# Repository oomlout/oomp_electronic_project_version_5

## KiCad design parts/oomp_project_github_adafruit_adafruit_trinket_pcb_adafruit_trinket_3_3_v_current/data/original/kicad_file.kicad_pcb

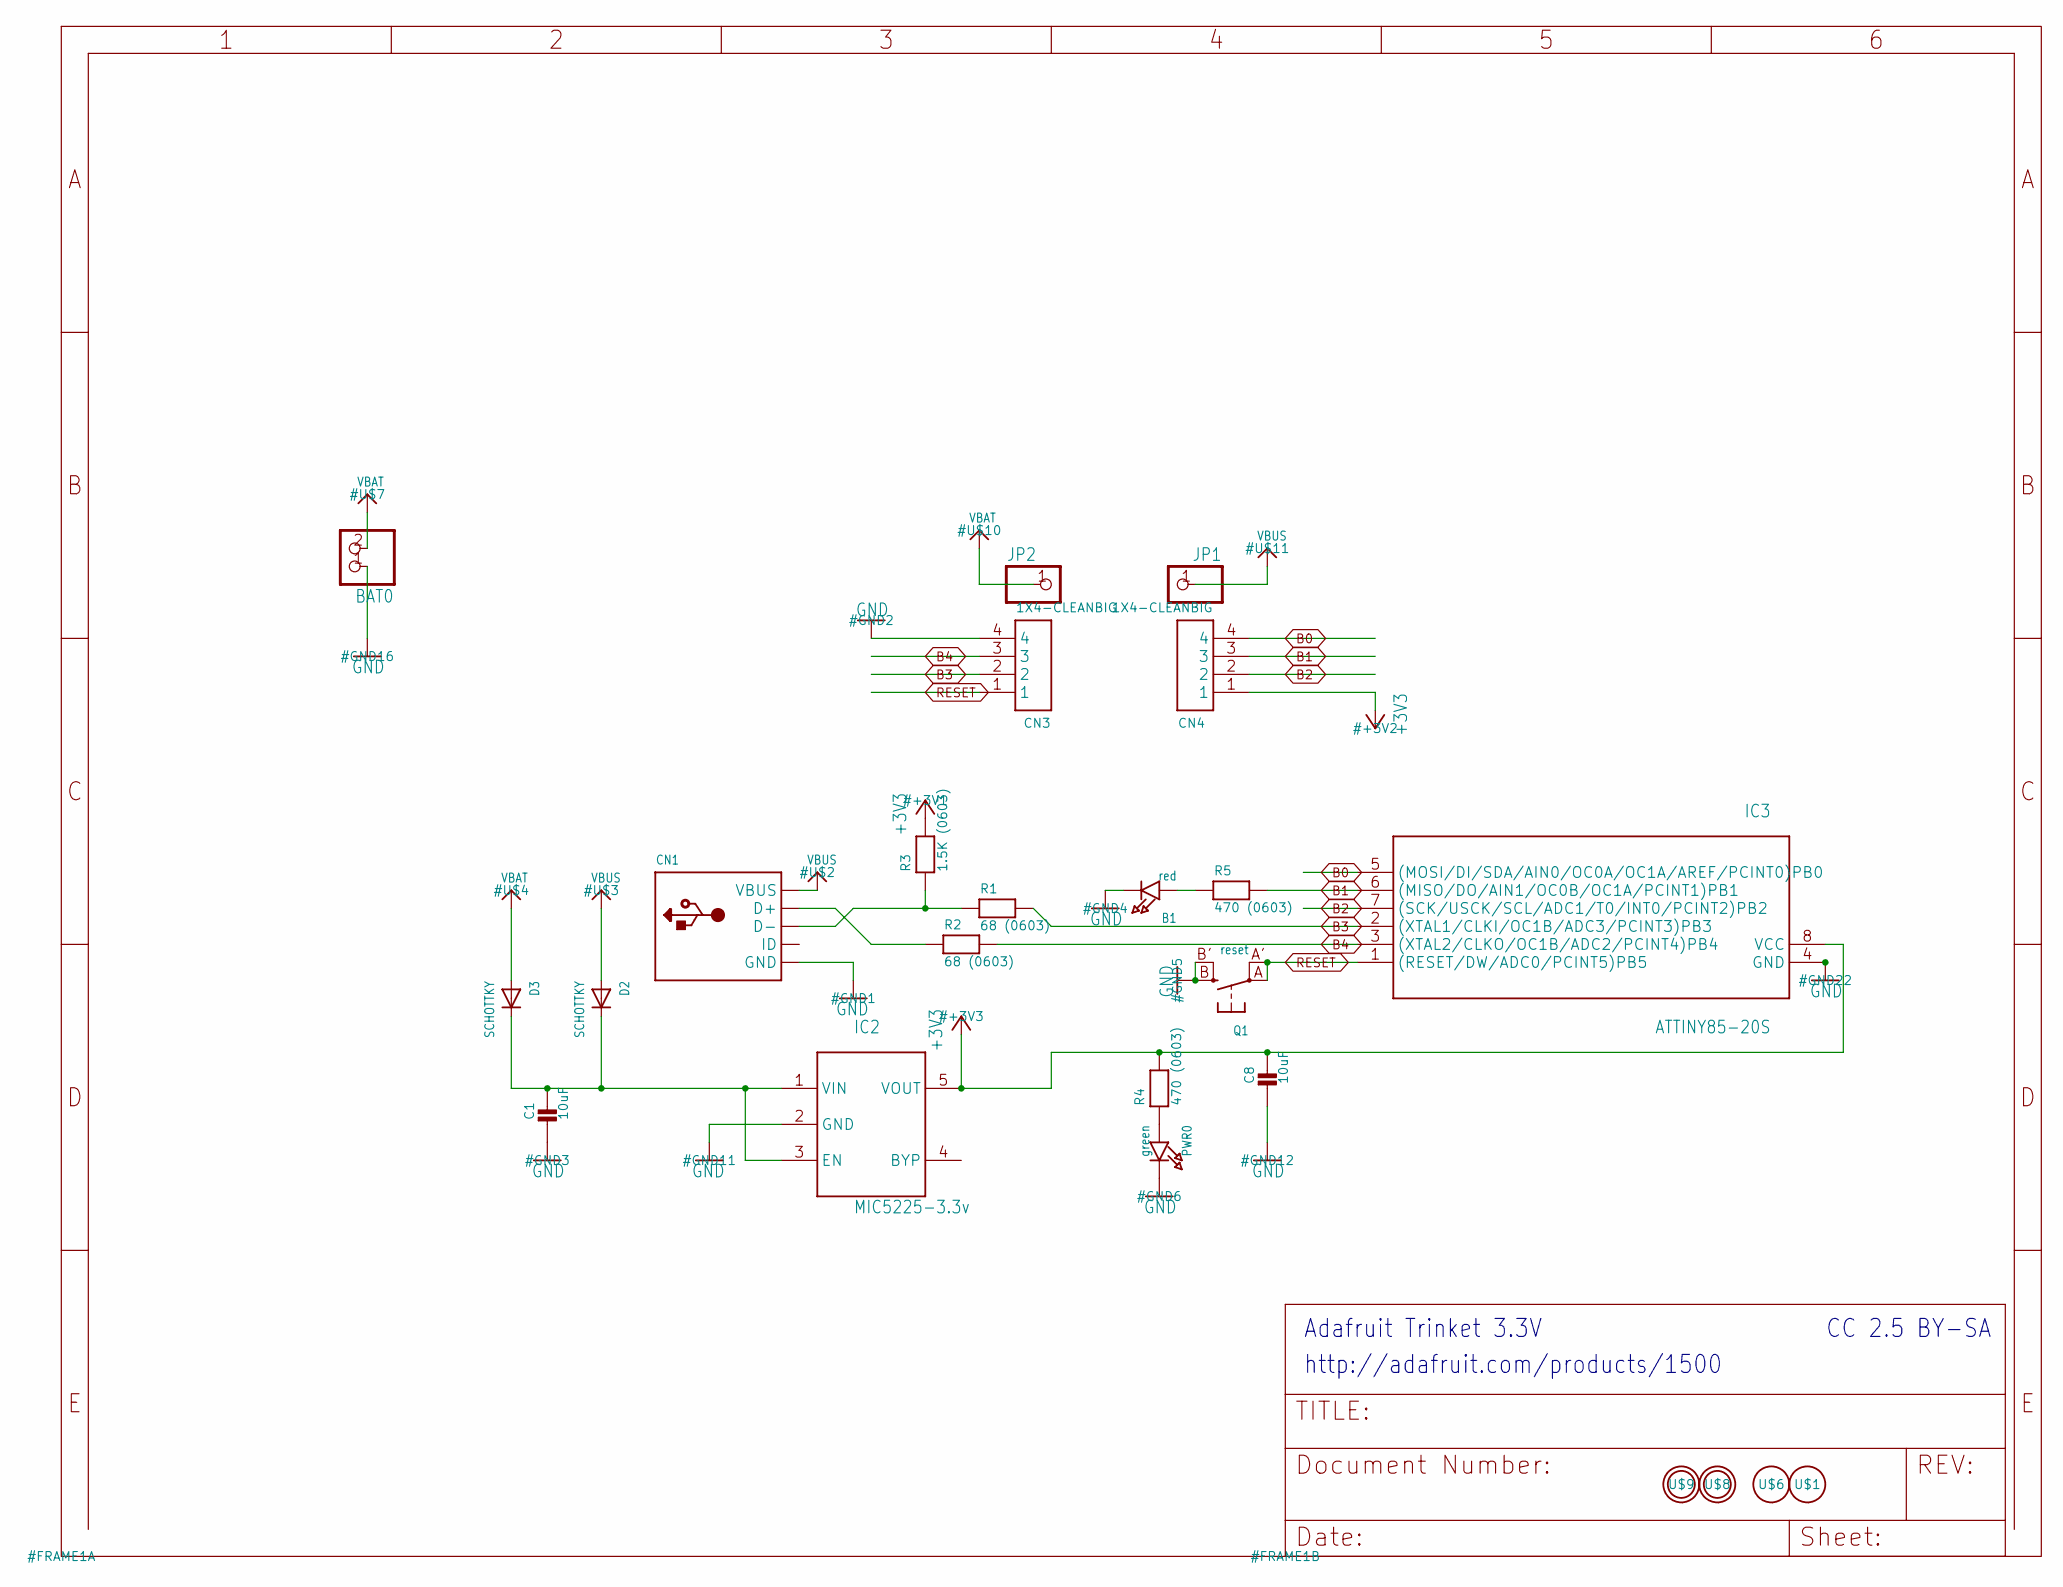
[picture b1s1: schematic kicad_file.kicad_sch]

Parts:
B1: red; CHIPLED_0805_NOOUTLINE
BAT0: CON_JST_PH_2PIN; JSTPH2
C1, C8: 10uF; 0805-NO
CN1: USBMINIB; USB-MINIB
CN3, CN4: 1X4-CLEANBIG; 1X04-CLEANBIG
D2, D3: SCHOTTKY; SOD-123FL
IC2: MIC5225-3.3v; SOT23-5L
IC3: ATTINY85-20S; SOIC8
JP1, JP2: PINHD-1X1CB; 1X01-CLEANBIG
PWR0: green; CHIPLED_0805_NOOUTLINE
Q1: reset; BTN_KMR2_4.6X2.8
R1, R2: 68 (0603); 0603-NO
R3: 1.5K (0603); 0603-NO
R4, R5: 470 (0603); 0603-NO
U$1, U$6: FIDUCIAL; FIDUCIAL_1MM
U$8, U$9: MOUNTINGHOLE2.0; MOUNTINGHOLE_2.0_PLATED

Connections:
+3V3: C8.1, CN4.1, IC2.5 (VOUT), IC3.8 (VCC), R3.2, R4.2
B0: CN4.4, IC3.5 ((MOSI/DI/SDA/AIN0/OC0A/OC1A/AREF/PCINT0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)
B1: CN4.3, IC3.6 ((MISO/DO/AIN1/OC0B/OC1A/PCINT1)PB1), R5.2
B2: CN4.2, IC3.7 ((SCK/USCK/SCL/ADC1/T0/INT0/PCINT2)PB2)
B3: CN3.2, IC3.2 ((XTAL1/CLKI/OC1B/ADC3/PCINT3)PB3), R1.2
B4: CN3.3, IC3.3 ((XTAL2/CLKO/OC1B/ADC2/PCINT4)PB4), R2.2
D+: CN1.D+, R2.1
D-: CN1.D-, R1.1, R3.1
GND: B1.C, BAT0.1, C1.2, C8.2, CN1.GND, CN1.GND1 (GND), CN1.GND2 (GND), CN1.GND3 (GND), CN1.GND4 (GND), CN3.4, IC2.2 (GND), IC3.4 (GND), PWR0.C, Q1.B (S), Q1.B' (S1)
unnamed: B1.A, R5.1
unnamed: PWR0.A, R4.1
unnamed: C1.1, D2.C, D3.C, IC2.1 (VIN), IC2.3 (EN)
RESET: CN3.1, IC3.1 ((RESET/DW/ADC0/PCINT5)PB5), Q1.A, Q1.A' (P1)
VBAT: BAT0.2, D3.A, JP2.1
VBUS: CN1.VBUS, D2.A, JP1.1

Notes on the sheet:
CC 2.5 BY-SA
http://adafruit.com/products/1500
Adafruit Trinket 3.3V

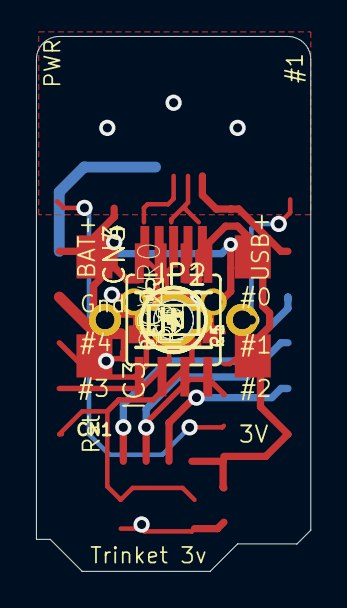
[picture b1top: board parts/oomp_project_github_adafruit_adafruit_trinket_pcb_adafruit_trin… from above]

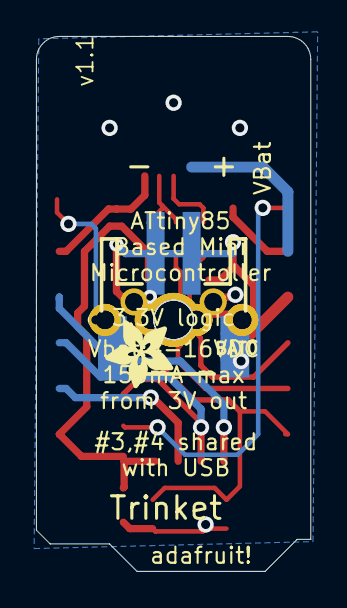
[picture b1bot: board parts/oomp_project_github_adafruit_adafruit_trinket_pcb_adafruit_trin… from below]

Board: 16 copper layers, 15.2 x 29.7 mm, 27 parts (2 on the bottom side), 15 nets.

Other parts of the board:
U$5: ADAFRUIT_3.5MM
UNK_HOLE_0: dummyfp0
UNK_HOLE_1: dummyfp1

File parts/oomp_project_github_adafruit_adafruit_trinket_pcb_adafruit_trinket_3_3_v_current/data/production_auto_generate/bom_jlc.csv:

Comment,Designator,Footprint,LCSC Part #
,"JP1,JP2",Adafruit Trinket 3.3V-import-fps:1X01-CLEANBIG,C7501259
,U$5,Adafruit Trinket 3.3V-import-fps:ADAFRUIT_3.5MM,
,BAT0,Adafruit Trinket 3.3V-import-fps:JSTPH2,
,CN1,Adafruit Trinket 3.3V-import-fps:USB-MINIB,
1.5K (0603),R3,Adafruit Trinket 3.3V-import-fps:0603-NO,C2930050
10uF,"C1,C8",Adafruit Trinket 3.3V-import-fps:0805-NO,
1X4-CLEANBIG,"CN3,CN4",Adafruit Trinket 3.3V-import-fps:1X04-CLEANBIG,
470 (0603),"R4,R5",Adafruit Trinket 3.3V-import-fps:0603-NO,C23179
68 (0603),"R1,R2",Adafruit Trinket 3.3V-import-fps:0603-NO,C27592
ATTINY85-20S,IC3,Adafruit Trinket 3.3V-import-fps:SOIC8,
FIDUCIAL,"U$1,U$6",Adafruit Trinket 3.3V-import-fps:FIDUCIAL_1MM,
green,PWR0,Adafruit Trinket 3.3V-import-fps:CHIPLED_0805_NOOUTLINE,
MIC5225-3.3v,IC2,Adafruit Trinket 3.3V-import-fps:SOT23-5L,
red,B1,Adafruit Trinket 3.3V-import-fps:CHIPLED_0805_NOOUTLINE,
reset,Q1,Adafruit Trinket 3.3V-import-fps:BTN_KMR2_4.6X2.8,
SCHOTTKY,"D2,D3",Adafruit Trinket 3.3V-import-fps:SOD-123FL,

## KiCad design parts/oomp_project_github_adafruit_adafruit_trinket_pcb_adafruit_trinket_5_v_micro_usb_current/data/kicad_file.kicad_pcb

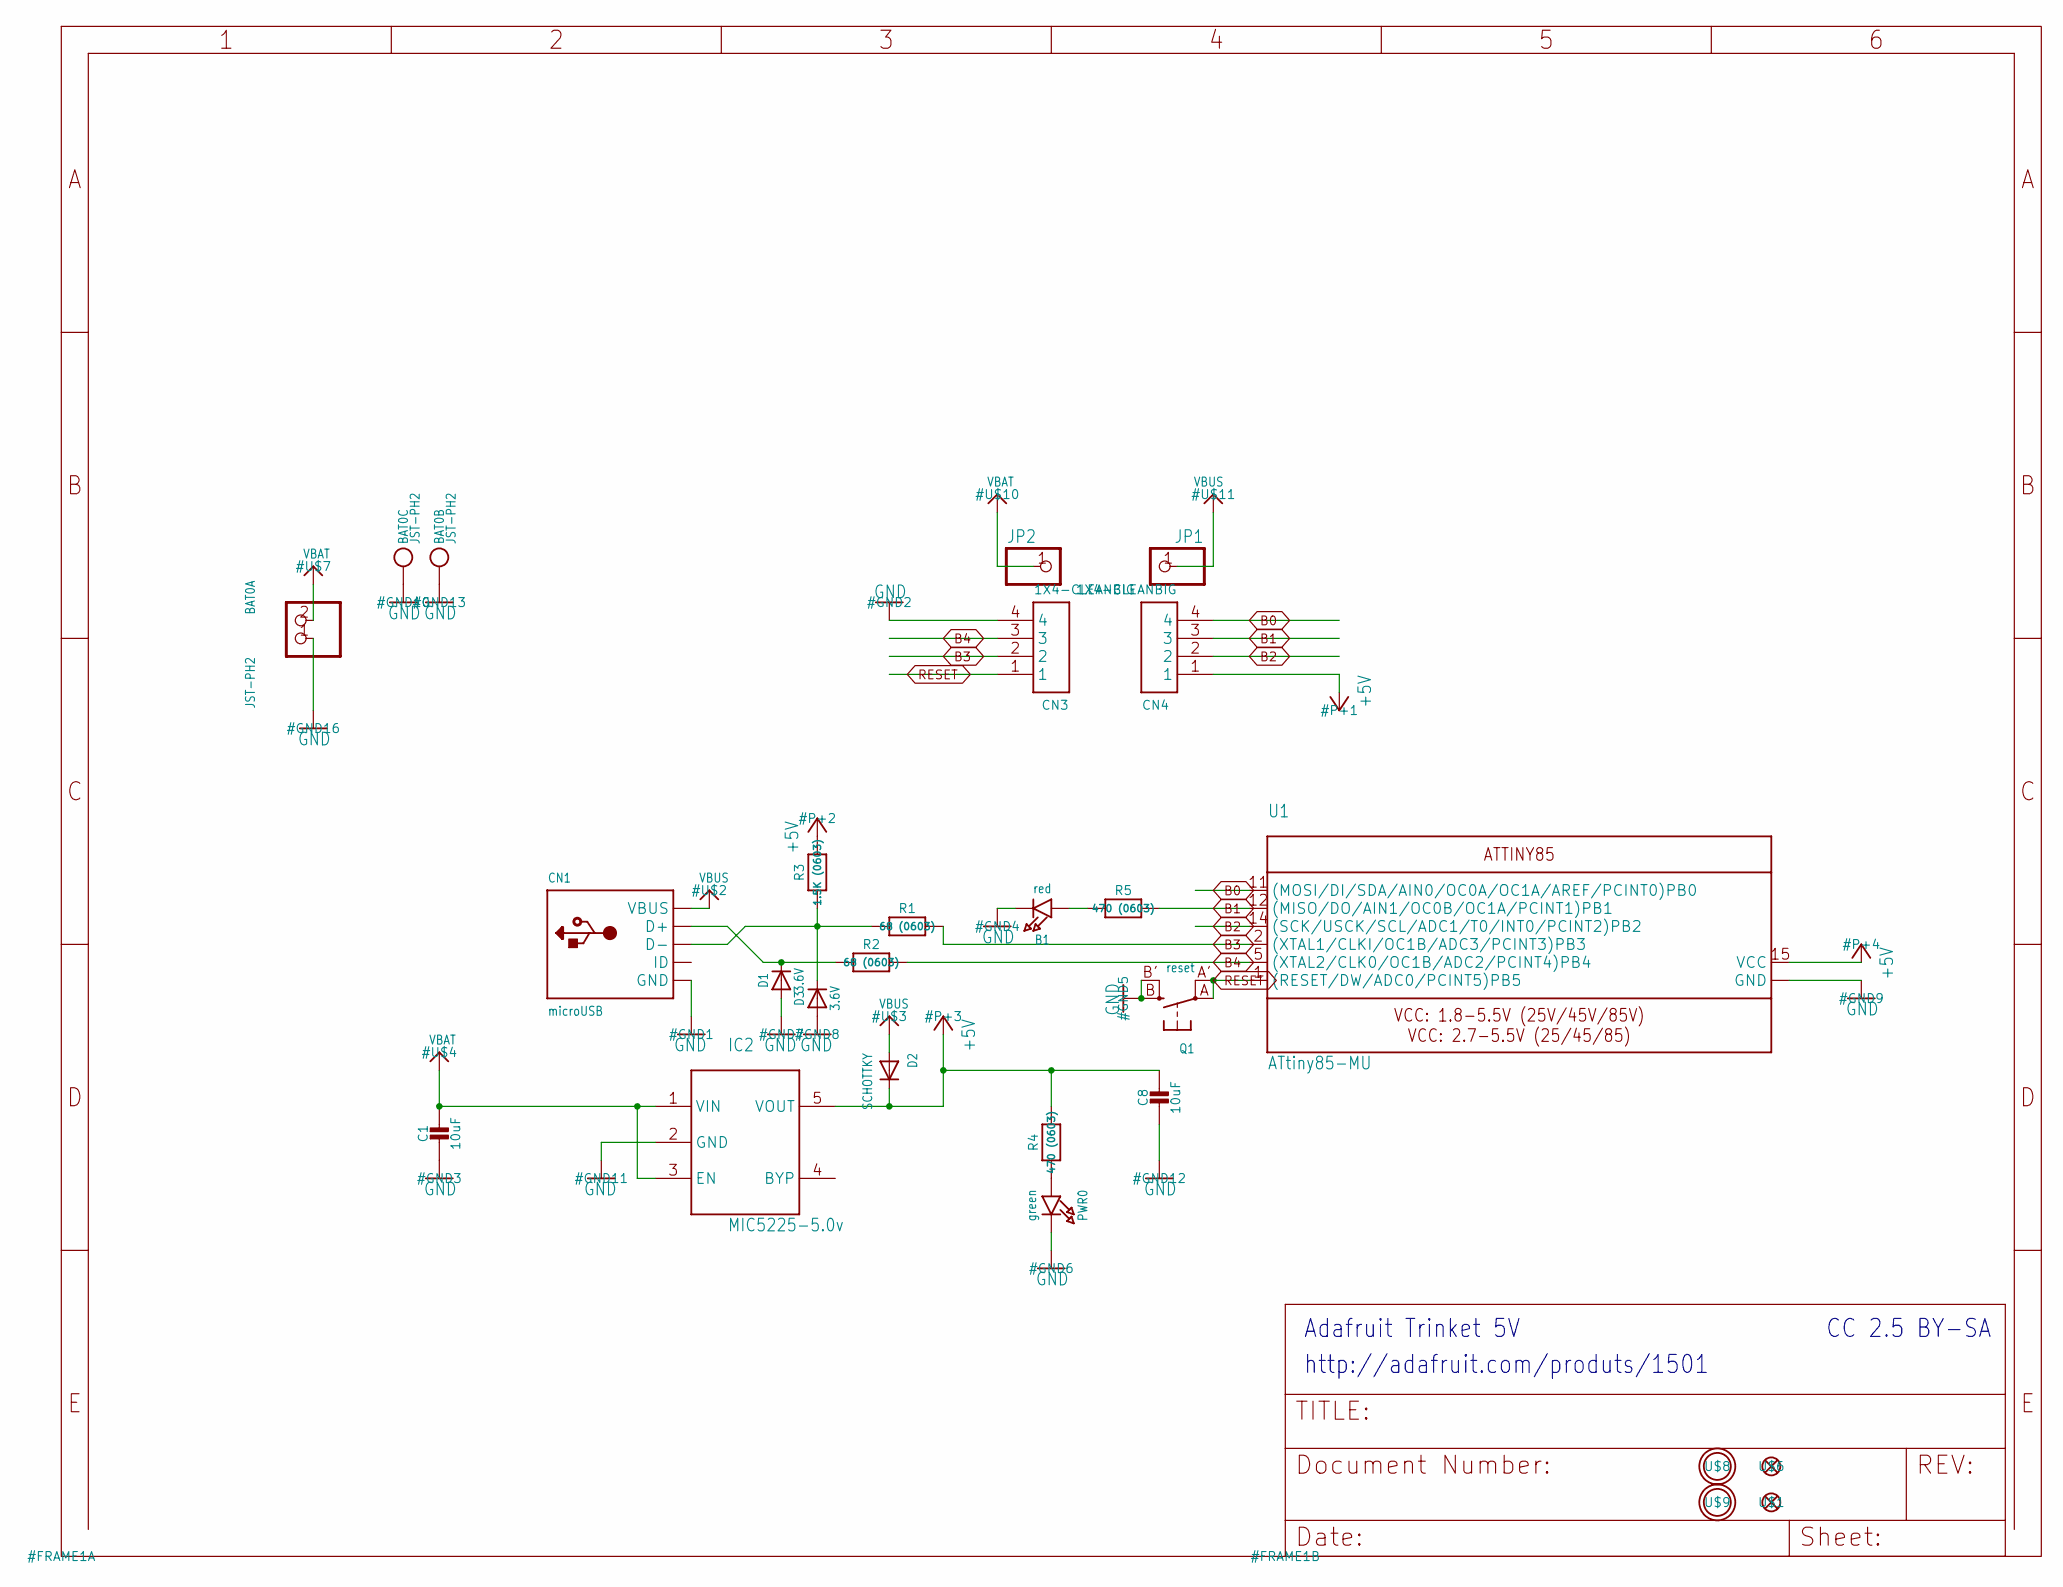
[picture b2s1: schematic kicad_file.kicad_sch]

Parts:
B1: red; CHIPLED_0805_NOOUTLINE
BAT0: JST-PH2; JSTPH2
C1, C8: 10uF; 0805-NO
CN1: microUSB; 4UCONN_20329
CN3, CN4: 1X4-CLEANBIG; 1X04-CLEANBIG
D1, D3: 3.6V; SOD-323
D2: SCHOTTKY; SOD-123FL
IC2: MIC5225-5.0v; SOT23-5L
JP1, JP2: PINHD-1X1CB; 1X01-CLEANBIG
PWR0: green; CHIPLED_0805_NOOUTLINE
Q1: reset; BTN_KMR2_4.6X2.8
R1, R2: 68 (0603); 0603-NO
R3: 1.5K (0603); 0603-NO
R4, R5: 470 (0603); 0603-NO
U1: ATtiny85-MU; MLF20_4X4MM_0.5MM_ATMEL
U$1, U$6: FIDUCIAL""; FIDUCIAL_1MM
U$8, U$9: MOUNTINGHOLE2.0; MOUNTINGHOLE_2.0_PLATED

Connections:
+5V: C8.1, CN4.1, D2.C, IC2.5 (VOUT), R3.2, R4.2, U1.15 (VCC)
B0: CN4.4, U1.11 ((MOSI/DI/SDA/AIN0/OC0A/OC1A/AREF/PCINT0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)
B1: CN4.3, R5.2, U1.12 ((MISO/DO/AIN1/OC0B/OC1A/PCINT1)PB1)
B2: CN4.2, U1.14 ((SCK/USCK/SCL/ADC1/T0/INT0/PCINT2)PB2)
B3: CN3.2, R1.2, U1.2 ((XTAL1/CLKI/OC1B/ADC3/PCINT3)PB3)
B4: CN3.3, R2.2, U1.5 ((XTAL2/CLK0/OC1B/ADC2/PCINT4)PB4)
GND: B1.C, BAT0.1, BAT0.NC1, BAT0.NC2, C1.2, C8.2, CN1.BASE@1 (GND), CN1.BASE@2 (GND), CN1.GND, CN1.SPRT@1 (GND), CN1.SPRT@2 (GND), CN1.SPRT@3 (GND), CN1.SPRT@4 (GND), CN3.4, D1.A, D3.A, IC2.2 (GND), PWR0.C, Q1.B (S), Q1.B' (S1), U1.8 (GND), U1.THERMAL (GND)
unnamed: B1.A, R5.1
unnamed: CN1.D+, D1.C, R2.1
unnamed: CN1.D-, D3.C, R1.1, R3.1
unnamed: PWR0.A, R4.1
RESET: CN3.1, Q1.A, Q1.A' (P1), U1.1 ((RESET/DW/ADC0/PCINT5)PB5)
VBAT: BAT0.2, C1.1, IC2.1 (VIN), IC2.3 (EN), JP2.1
VBUS: CN1.VBUS, D2.A, JP1.1

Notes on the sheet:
CC 2.5 BY-SA
http://adafruit.com/produts/1501
Adafruit Trinket 5V

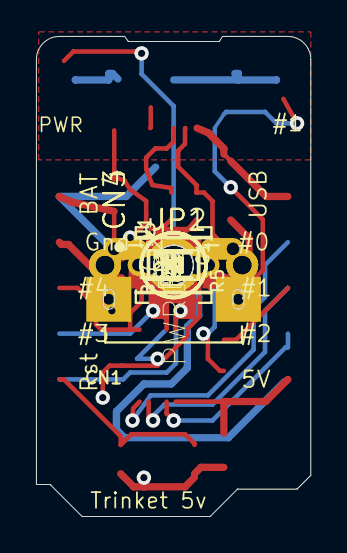
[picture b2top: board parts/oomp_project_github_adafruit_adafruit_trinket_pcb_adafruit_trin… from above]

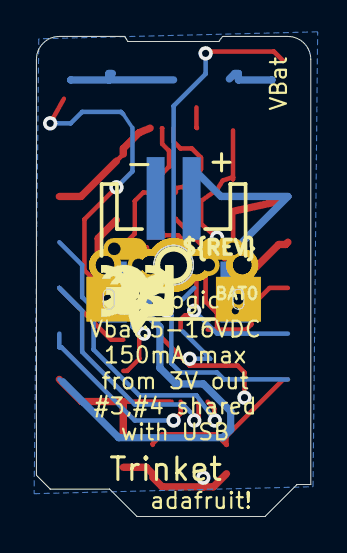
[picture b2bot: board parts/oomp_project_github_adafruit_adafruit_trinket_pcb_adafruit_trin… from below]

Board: 16 copper layers, 15.2 x 26.7 mm, 31 parts (5 on the bottom side), 14 nets.

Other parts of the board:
U$5: ADAFRUIT_3.5MM
U$12: PCBFEAT-REV-040
U$13: SYMBOL_FCC_TINY
U$14: SYMBOL_CE_TINY
UNK_HOLE_0: dummyfp0
UNK_HOLE_1: dummyfp1

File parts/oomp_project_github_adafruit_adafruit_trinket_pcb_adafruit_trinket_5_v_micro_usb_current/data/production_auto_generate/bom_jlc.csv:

Comment,Designator,Footprint,LCSC Part #
,"JP1,JP2",Adafruit Trinket 5V microUSB-import-fps:1X01-CLEANBIG,C7501259
,U$5,Adafruit Trinket 5V microUSB-import-fps:ADAFRUIT_3.5MM,
,U$12,Adafruit Trinket 5V microUSB-import-fps:PCBFEAT-REV-040,
,U$14,Adafruit Trinket 5V microUSB-import-fps:SYMBOL_CE_TINY,
,U$13,Adafruit Trinket 5V microUSB-import-fps:SYMBOL_FCC_TINY,
1.5K (0603),R3,Adafruit Trinket 5V microUSB-import-fps:0603-NO,C2930050
10uF,"C1,C8",Adafruit Trinket 5V microUSB-import-fps:0805-NO,
1X4-CLEANBIG,"CN3,CN4",Adafruit Trinket 5V microUSB-import-fps:1X04-CLEANBIG,
3.6V,"D1,D3",Adafruit Trinket 5V microUSB-import-fps:SOD-323,
470 (0603),"R4,R5",Adafruit Trinket 5V microUSB-import-fps:0603-NO,C23179
68 (0603),"R1,R2",Adafruit Trinket 5V microUSB-import-fps:0603-NO,C27592
ATtiny85-MU,U1,Adafruit Trinket 5V microUSB-import-fps:MLF20_4X4MM_0.5MM_ATMEL,
"FIDUCIAL""""","U$1,U$6",Adafruit Trinket 5V microUSB-import-fps:FIDUCIAL_1MM,
green,PWR0,Adafruit Trinket 5V microUSB-import-fps:CHIPLED_0805_NOOUTLINE,
JST-PH2,BAT0,Adafruit Trinket 5V microUSB-import-fps:JSTPH2,
MIC5225-5.0v,IC2,Adafruit Trinket 5V microUSB-import-fps:SOT23-5L,
microUSB,CN1,Adafruit Trinket 5V microUSB-import-fps:4UCONN_20329,
red,B1,Adafruit Trinket 5V microUSB-import-fps:CHIPLED_0805_NOOUTLINE,
reset,Q1,Adafruit Trinket 5V microUSB-import-fps:BTN_KMR2_4.6X2.8,
SCHOTTKY,D2,Adafruit Trinket 5V microUSB-import-fps:SOD-123FL,

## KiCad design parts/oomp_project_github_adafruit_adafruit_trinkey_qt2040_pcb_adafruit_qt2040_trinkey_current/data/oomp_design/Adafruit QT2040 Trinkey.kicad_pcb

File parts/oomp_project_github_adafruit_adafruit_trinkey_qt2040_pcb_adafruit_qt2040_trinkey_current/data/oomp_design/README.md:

# OOMP KiCad design copy

Open `Adafruit QT2040 Trinkey.kicad_pro` (or the `.kicad_pcb` / `.kicad_sch`) in KiCad. Local OOMP libraries are under `libraries/`. Original inputs are preserved in [../original/](../original/).

Only verified unchanged installed KiCad defaults were renamed. Modified, custom, unmatched and unavailable items remain unchanged. Soldering variants are never swapped during conversion. Existing pad coordinates, nets and UUIDs are preserved.

See [conversion_report.yaml](conversion_report.yaml) for every conversion and skip. Copy this directory before editing; regeneration refuses to overwrite edited design files.

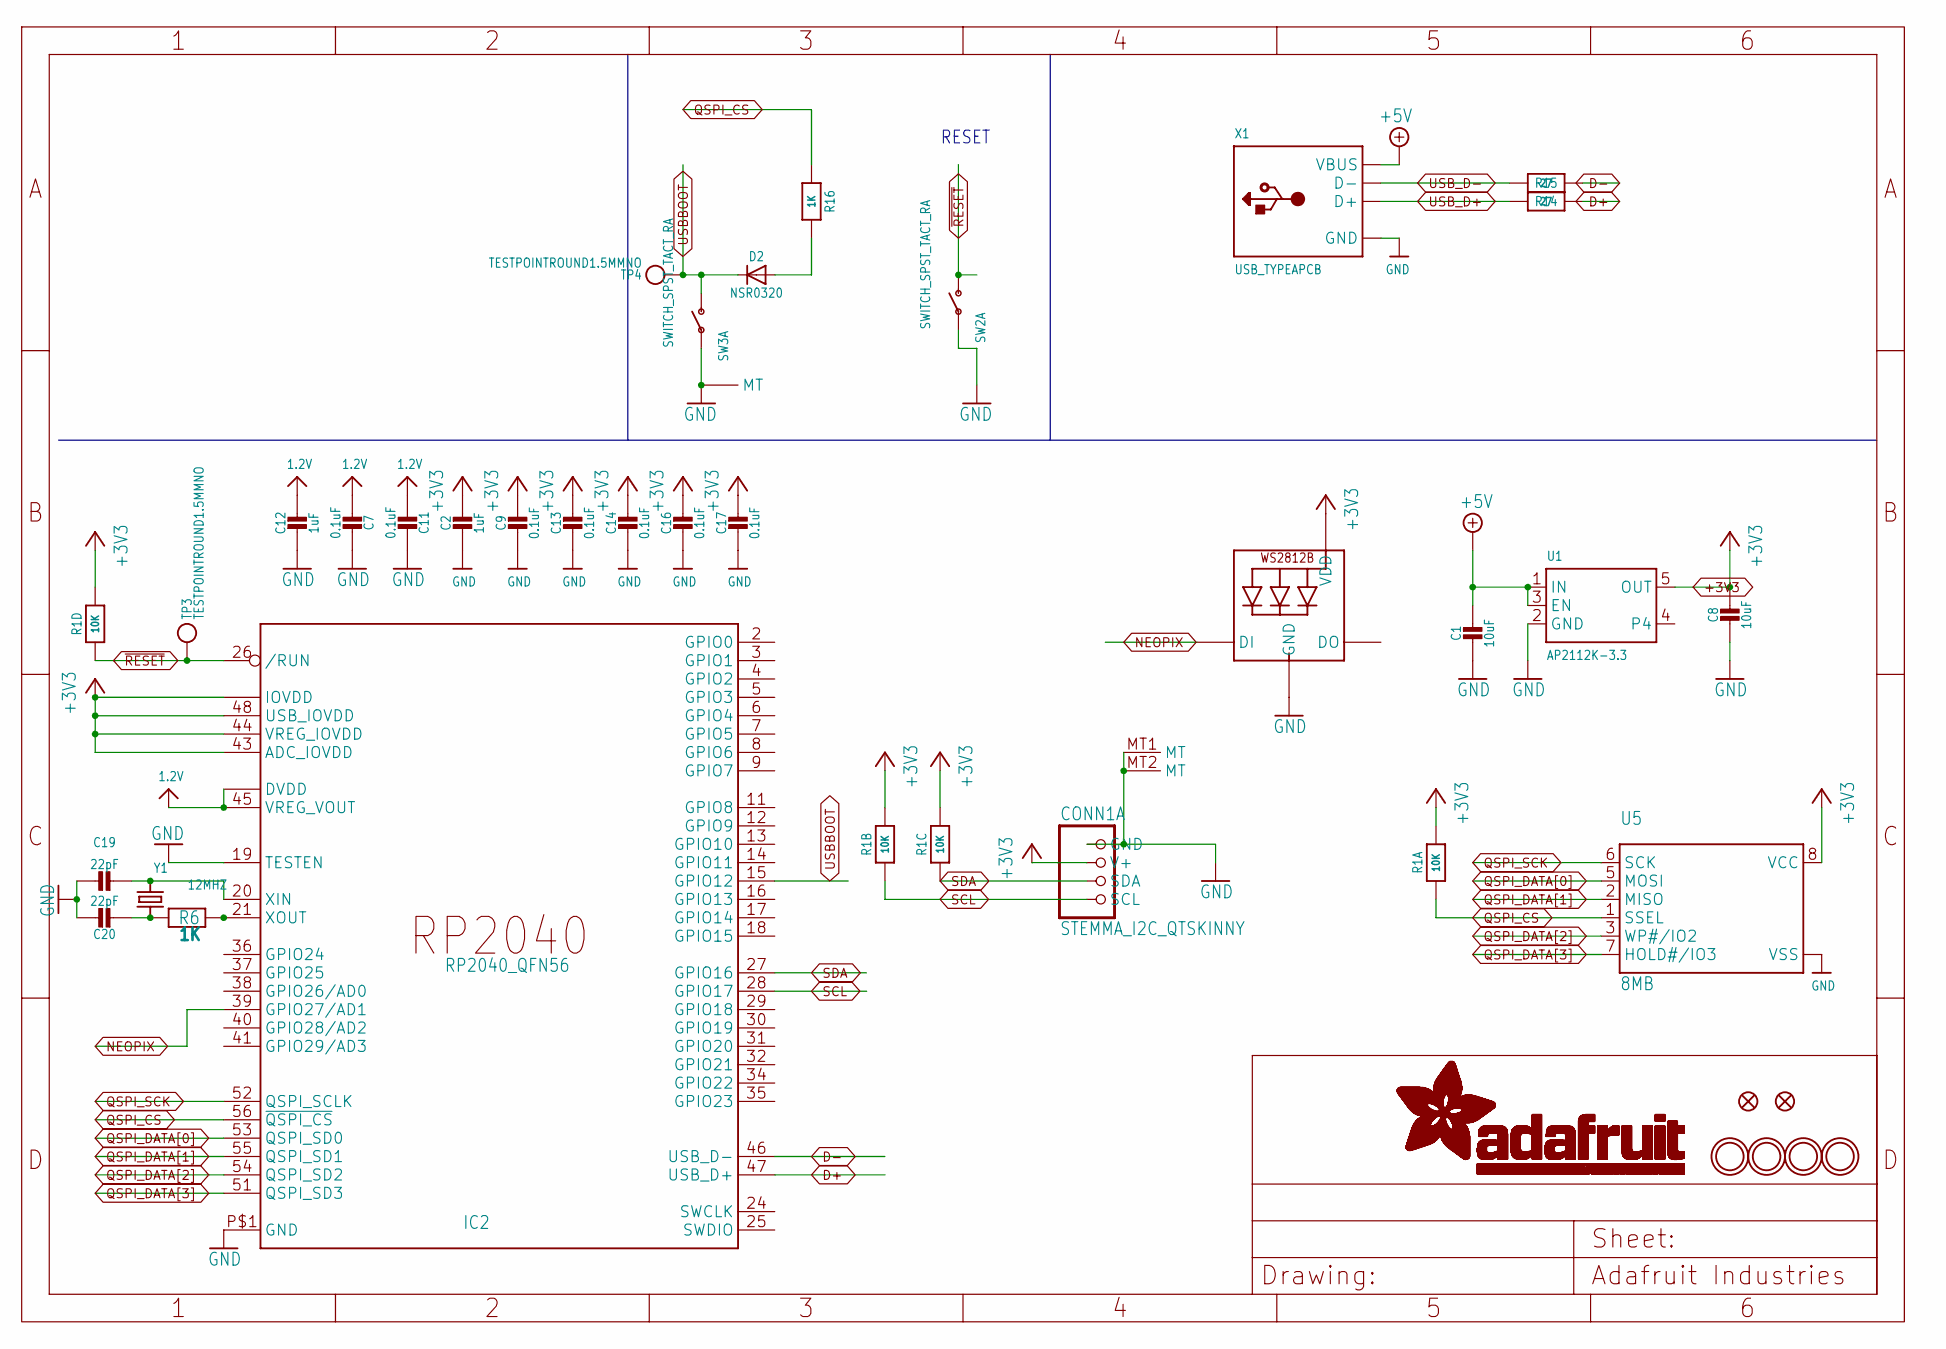
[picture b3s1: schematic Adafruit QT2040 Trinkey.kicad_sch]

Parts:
C1, C8: 10uF; 0805-NO
C2, C12: 1uF; 0603-NO
C7: 0.1uF; _0603MP
C9, C11, C13, C14, C16, C17: 0.1uF; 0603-NO
C19, C20: 22pF; 0603-NO
CONN1: STEMMA_I2C_QTSKINNY; JST_SH4_SKINNY
D2: NSR0320; SOD-323_MINI
IC2: RP2040_QFN56; QFN56_7MM_REDUCEDEPAD
LED1: WS2812B_SK6805_1515; SK6805_1515
R1: 10K; RESPACK_4X0603
R6, R16: 1K; 0603-NO
R14, R15: 27; 0603-NO
SW2, SW3: SWITCH_SPST_TACT_RA; SPST_TACTILE_RA
TP3, TP4: TESTPOINTROUND1.5MMNO; TESTPOINT_ROUND_1.5MM_NO
U1: AP2112K-3.3; SOT23-5
U5: 8MB; USON8_4X4
U$1, U$2, U$4, U$5: MOUNTINGHOLE2.5; MOUNTINGHOLE_2.5_PLATED
U$6, U$8: FIDUCIAL_1MM
X1: USB_TYPEAPCB; USBA_PCB
Y1: 12MHZ; CRYSTAL_2.5X2

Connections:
1.2V: C7.2, C11.2, C12.1, IC2.23 (DVDD), IC2.45 (VREG_VOUT), IC2.50 (DVDD)
+3V3: C2.1, C8.1, C9.1, C13.1, C14.1, C16.1, C17.1, CONN1.2 (V+), IC2.1 (IOVDD), IC2.10 (IOVDD), IC2.22 (IOVDD), IC2.33 (IOVDD), IC2.42 (IOVDD), IC2.43 (ADC_IOVDD), IC2.44 (VREG_IOVDD), IC2.48 (USB_IOVDD), IC2.49 (IOVDD), LED1.2 (VDD), R1.5 (2), R1.6 (2), R1.7 (2), R1.8 (2), U1.5 (OUT), U5.8 (VCC)
+5V: C1.1, U1.1 (IN), U1.3 (EN), X1.VCC (VBUS)
D+: IC2.47 (USB_D+), R15.2
D-: IC2.46 (USB_D-), R14.2
GND: C1.2, C2.2, C7.1, C8.2, C9.2, C11.1, C12.2, C13.2, C14.2, C16.2, C17.2, C19.1, C20.1, CONN1.1 (GND), CONN1.MT1 (MT), CONN1.MT2 (MT), IC2.19 (TESTEN), IC2.P$1 (GND), LED1.4 (GND), SW2.1, SW3.1, SW3.MT1 (MT), SW3.MT2 (MT), U1.2 (GND), U5.4 (VSS), U5.PAD (VSS), X1.GND
unnamed: D2.A, R16.2
unnamed: C19.2, IC2.20 (XIN), Y1.3 (2)
unnamed: C20.2, R6.1, Y1.1
unnamed: IC2.21 (XOUT), R6.2
NEOPIX: IC2.39 (GPIO27/AD1), LED1.1 (DI)
QSPI_CS: IC2.56 (~QSPI_CS), R1.1, R16.1, U5.1 (SSEL)
QSPI_DATA[0]: IC2.53 (QSPI_SD0), U5.5 (MOSI)
QSPI_DATA[1]: IC2.55 (QSPI_SD1), U5.2 (MISO)
QSPI_DATA[2]: IC2.54 (QSPI_SD2), U5.3 (WP#/IO2)
QSPI_DATA[3]: IC2.51 (QSPI_SD3), U5.7 (HOLD#/IO3)
QSPI_SCK: IC2.52 (QSPI_SCLK), U5.6 (SCK)
SCL: CONN1.4 (SCL), IC2.28 (GPIO17), R1.2 (1)
SDA: CONN1.3 (SDA), IC2.27 (GPIO16), R1.3 (1)
USBBOOT: D2.C, IC2.15 (GPIO12), SW3.2 (S), TP4.P$1
USB_D+: R15.1, X1.USB_PLUS (D+)
USB_D-: R14.1, X1.USB_NEG (D-)
~RESET: IC2.26 (/RUN), R1.4 (1), SW2.2 (S), TP3.P$1

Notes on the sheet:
RESET

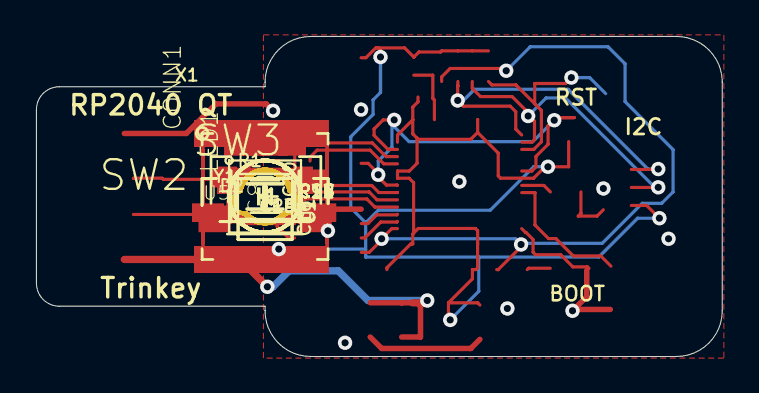
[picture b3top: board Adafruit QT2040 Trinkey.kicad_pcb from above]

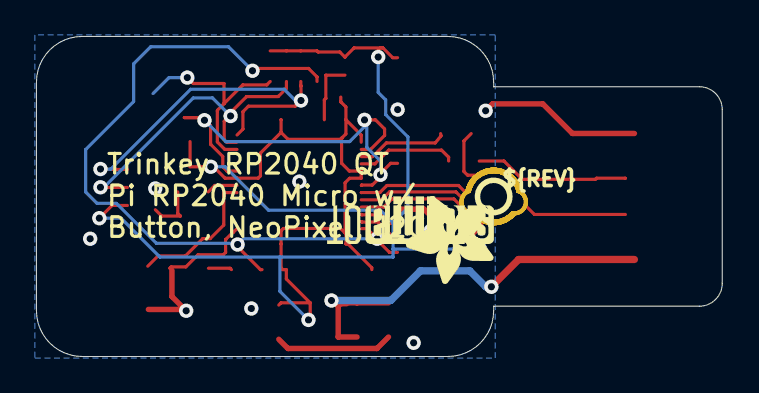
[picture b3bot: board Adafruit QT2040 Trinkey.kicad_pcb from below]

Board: 16 copper layers, 38.1 x 17.8 mm, 39 parts (5 on the bottom side), 23 nets.

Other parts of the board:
U$7: STEMMAQT
U$9: PCBFEAT-REV-040
U$10: ADAFRUIT_5MM

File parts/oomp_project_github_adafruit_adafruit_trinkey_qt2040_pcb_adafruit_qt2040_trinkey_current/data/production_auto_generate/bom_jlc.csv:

Comment,Designator,Footprint,LCSC Part #
,U$10,Adafruit QT2040 Trinkey-import-fps:ADAFRUIT_5MM,
,U$9,Adafruit QT2040 Trinkey-import-fps:PCBFEAT-REV-040,
,"SW2,SW3",Adafruit QT2040 Trinkey-import-fps:SPST_TACTILE_RA,
,U$7,Adafruit QT2040 Trinkey-import-fps:STEMMAQT,
,"TP3,TP4",Adafruit QT2040 Trinkey-import-fps:TESTPOINT_ROUND_1.5MM_NO,
,X1,Adafruit QT2040 Trinkey-import-fps:USBA_PCB,
  NSR0320,D2,Adafruit QT2040 Trinkey-import-fps:SOD-323_MINI,
0.1uF,"C9,C11,C13,C14,C16,C17",Adafruit QT2040 Trinkey-import-fps:0603-NO,C14663
0.1uF,C7,Adafruit QT2040 Trinkey-import-fps:_0603MP,C14663
10K,R1,Adafruit QT2040 Trinkey-import-fps:RESPACK_4X0603,C98220
10uF,"C1,C8",Adafruit QT2040 Trinkey-import-fps:0805-NO,
12MHZ,Y1,Adafruit QT2040 Trinkey-import-fps:CRYSTAL_2.5X2,
1K,"R6,R16",Adafruit QT2040 Trinkey-import-fps:0603-NO,C2907002
1uF,"C2,C12",Adafruit QT2040 Trinkey-import-fps:0603-NO,C5673
22pF,"C19,C20",Adafruit QT2040 Trinkey-import-fps:0603-NO,C105620
27,"R14,R15",Adafruit QT2040 Trinkey-import-fps:0603-NO,C25190
8MB,U5,Adafruit QT2040 Trinkey-import-fps:USON8_4X4,
AP2112K-3.3,U1,Adafruit QT2040 Trinkey-import-fps:SOT23-5,
FIDUCIAL_1MM,"U$6,U$8",Adafruit QT2040 Trinkey-import-fps:FIDUCIAL_1MM,
RP2040_QFN56,IC2,Adafruit QT2040 Trinkey-import-fps:QFN56_7MM_REDUCEDEPAD,
STEMMA_I2C_QTSKINNY,CONN1,Adafruit QT2040 Trinkey-import-fps:JST_SH4_SKINNY,
WS2812B_SK6805_1515,LED1,Adafruit QT2040 Trinkey-import-fps:SK6805_1515,
